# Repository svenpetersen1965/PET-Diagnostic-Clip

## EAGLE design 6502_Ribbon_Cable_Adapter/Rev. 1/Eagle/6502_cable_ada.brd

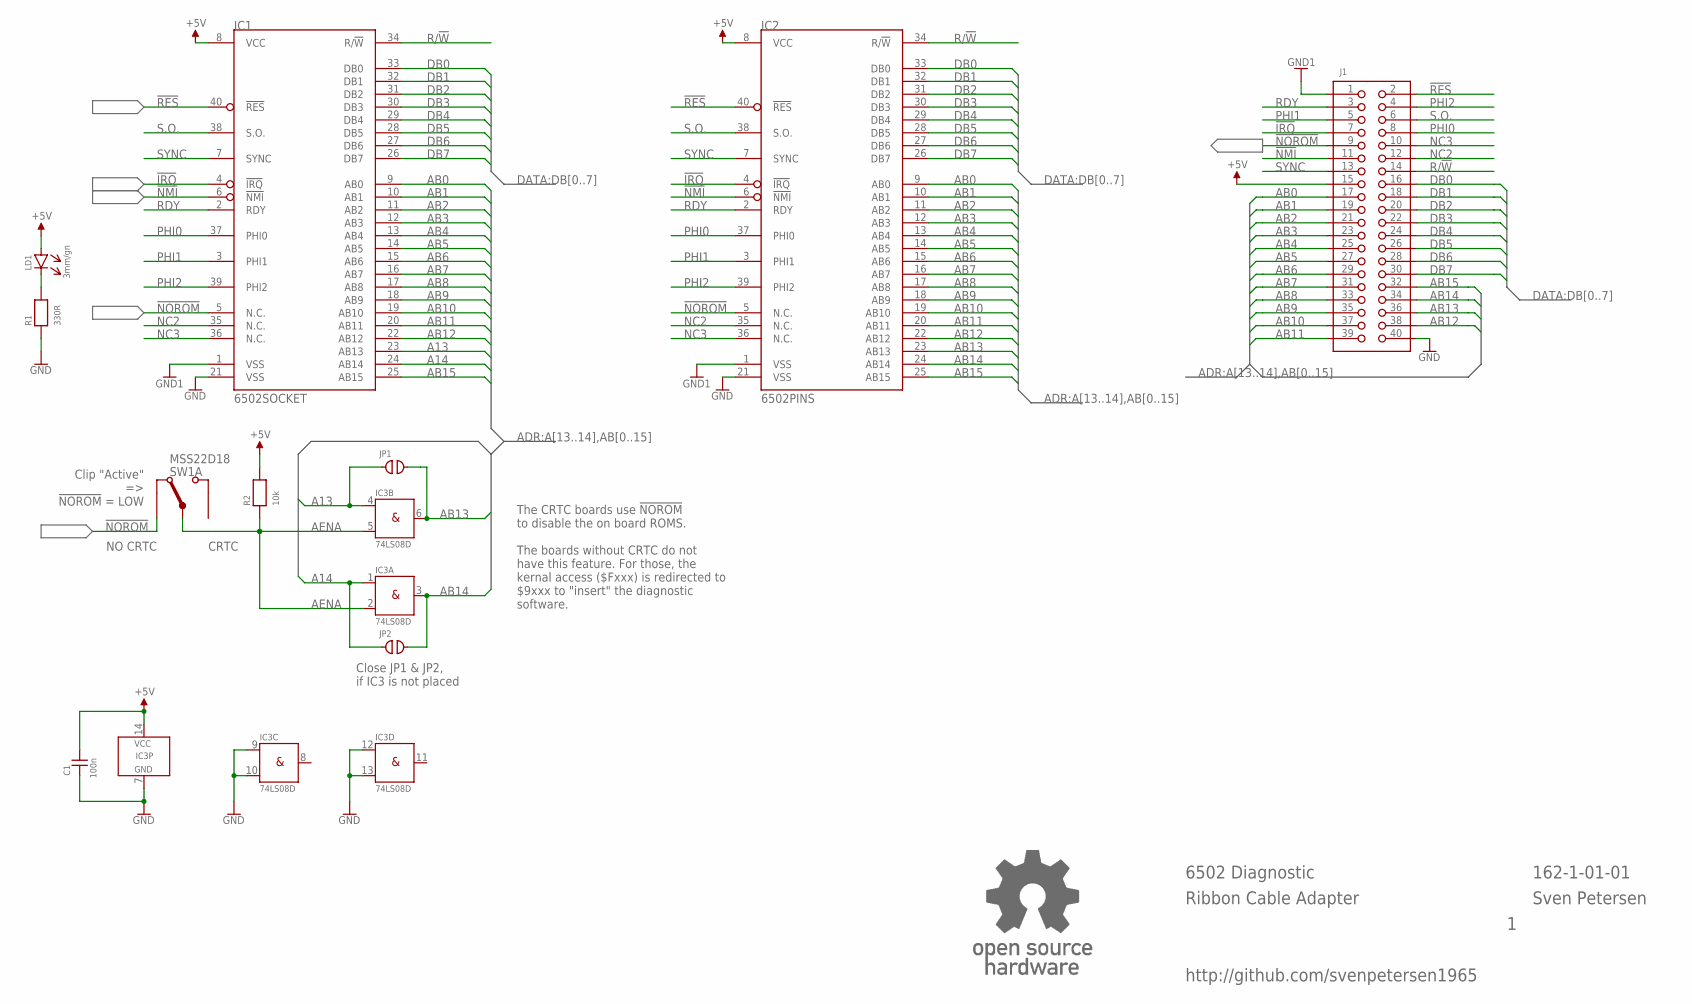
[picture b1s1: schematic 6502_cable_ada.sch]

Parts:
C1: 100n; 0805
IC1: 6502SOCKET; GS40P
IC2: 6502PINS; DIL40_PINS_SS
IC3: 74LS08D; SO-14
J1: PINHD-2X20WV; 2X20WV
JP1, JP2: OPEN; CP_OP
LD1: 3mm/gn; 3MM
R1: 330R; 0805
R2: 10k; 0805
SW1: MSS22D18; DPDT_9MM
U$11: OPEN_SOURCE_HW; OPENHW

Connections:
!IRQ: IC1.4 (!IRQ), IC2.4 (!IRQ), J1.7
!NMI: IC1.6 (!NMI), IC2.6 (!NMI), J1.11
!NOROM: IC1.5 (N.C.), IC2.5 (N.C.), J1.9, SW1.3 (DWN)
!RES: IC1.40 (!RES), IC2.40 (!RES), J1.2
+5V: C1.2, IC1.8 (VCC), IC2.8 (VCC), IC3.14 (VCC), J1.15, LD1.A, R2.2
A13: IC1.23 (AB13), IC3.4 (I0), JP1.1
A14: IC1.24 (AB14), IC3.1 (I0), JP2.1
AB0: IC1.9 (AB0), IC2.9 (AB0), J1.17
AB1: IC1.10 (AB1), IC2.10 (AB1), J1.19
AB2: IC1.11 (AB2), IC2.11 (AB2), J1.21
AB3: IC1.12 (AB3), IC2.12 (AB3), J1.23
AB4: IC1.13 (AB4), IC2.13 (AB4), J1.25
AB5: IC1.14 (AB5), IC2.14 (AB5), J1.27
AB6: IC1.15 (AB6), IC2.15 (AB6), J1.29
AB7: IC1.16 (AB7), IC2.16 (AB7), J1.31
AB8: IC1.17 (AB8), IC2.17 (AB8), J1.33
AB9: IC1.18 (AB9), IC2.18 (AB9), J1.35
AB10: IC1.19 (AB10), IC2.19 (AB10), J1.37
AB11: IC1.20 (AB11), IC2.20 (AB11), J1.39
AB12: IC1.22 (AB12), IC2.22 (AB12), J1.38
AB13: IC2.23 (AB13), IC3.6 (O), J1.36, JP1.2
AB14: IC2.24 (AB14), IC3.3 (O), J1.34, JP2.2
AB15: IC1.25 (AB15), IC2.25 (AB15), J1.32
AENA: IC3.2 (I1), IC3.5 (I1), R2.1, SW1.2 (COM)
DB0: IC1.33 (DB0), IC2.33 (DB0), J1.16
DB1: IC1.32 (DB1), IC2.32 (DB1), J1.18
DB2: IC1.31 (DB2), IC2.31 (DB2), J1.20
DB3: IC1.30 (DB3), IC2.30 (DB3), J1.22
DB4: IC1.29 (DB4), IC2.29 (DB4), J1.24
DB5: IC1.28 (DB5), IC2.28 (DB5), J1.26
DB6: IC1.27 (DB6), IC2.27 (DB6), J1.28
DB7: IC1.26 (DB7), IC2.26 (DB7), J1.30
GND: C1.1, IC1.21 (VSS), IC2.21 (VSS), IC3.7 (GND), IC3.9 (I0), IC3.10 (I1), IC3.12 (I0), IC3.13 (I1), J1.40, R1.1
GND1: IC1.1 (VSS), IC2.1 (VSS), J1.1
unnamed: LD1.C (K), R1.2
NC2: IC1.35 (N.C.), IC2.35 (N.C.), J1.12
NC3: IC1.36 (N.C.), IC2.36 (N.C.), J1.10
PHI0: IC1.37 (PHI0), IC2.37 (PHI0), J1.8
PHI1: IC1.3 (PHI1), IC2.3 (PHI1), J1.5
PHI2: IC1.39 (PHI2), IC2.39 (PHI2), J1.4
R/!W: IC1.34 (R/!W), IC2.34 (R/!W), J1.14
RDY: IC1.2 (RDY), IC2.2 (RDY), J1.3
S.O.: IC1.38 (S.O.), IC2.38 (S.O.), J1.6
SYNC: IC1.7 (SYNC), IC2.7 (SYNC), J1.13

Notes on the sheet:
6502 Diagnostic
Ribbon Cable Adapter
Sven Petersen
162-1-01-01
http://github.com/svenpetersen1965
Close JP1 & JP2, if IC3 is not placed
Clip "Active" => !NOROM! = LOW
CRTC
NO CRTC
The CRTC boards use !NOROM! to disable the on board ROMS. The boards without CRTC do not have this feature. For those, the kernal access ($Fxxx) is redirected to $9xxx to "insert" the diagnostic software.

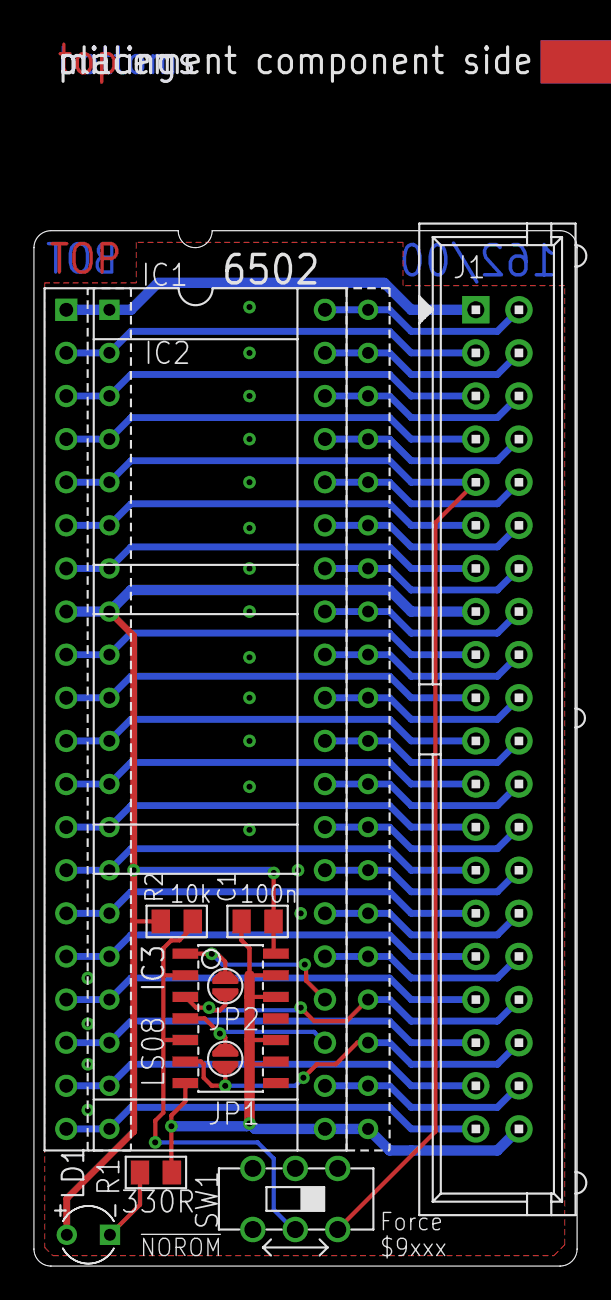
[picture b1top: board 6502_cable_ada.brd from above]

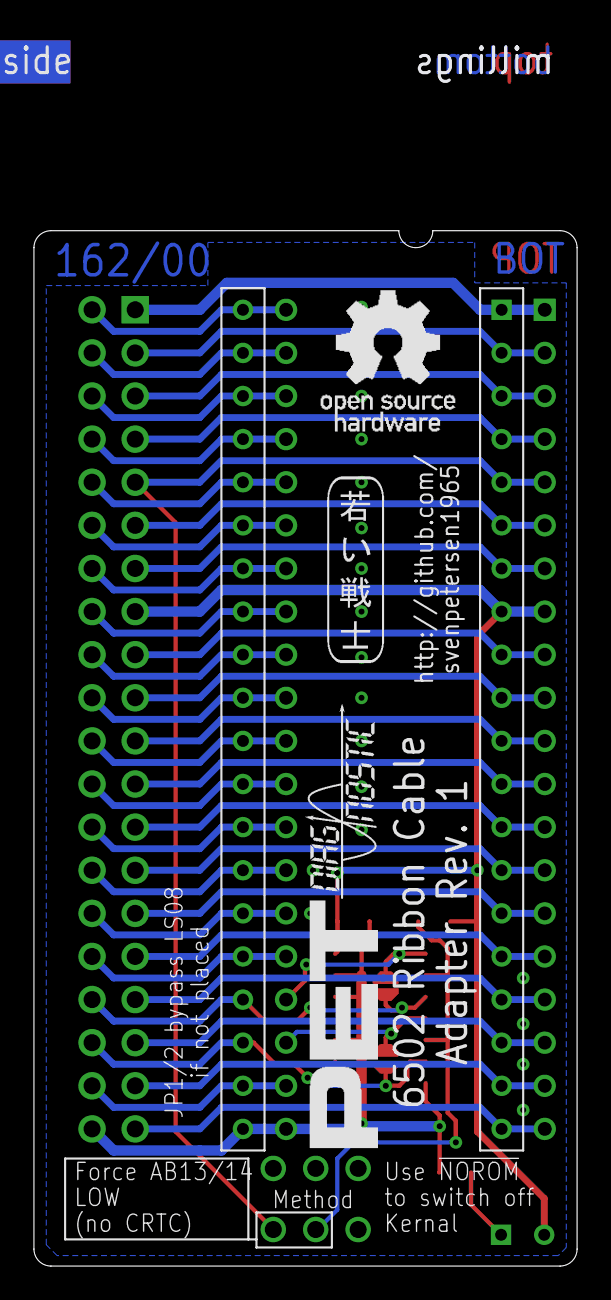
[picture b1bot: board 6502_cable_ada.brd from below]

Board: 2 copper layers, 32.0 x 61.0 mm, 17 parts (4 on the bottom side), 44 nets.

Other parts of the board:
U$12: PCB-TITLE/
U$13: 2LAYER
U$14: SVEN_TAG
U$17: DIAG_SMALL
U$29: PET

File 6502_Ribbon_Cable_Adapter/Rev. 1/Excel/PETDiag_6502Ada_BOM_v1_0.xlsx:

Commodore PET Diagnostic Clip: 6502 Ribbon Cable Adapter Rev. 1
Bill of Material Rev. 1.0
Pos. | Qty | Value | Footprint | Ref.-No. | Comment
1 | 1 | 162-2-01-01 | 2 Layer | PCB Rev. 1 | 2 layer, Cu 35µ, HASL, 61.0mm x 32.0mm, 1.6mm FR4
2 | 1 | 2x20 box header, 2.54mm pitch | 2X20WV | J1 | 2x20, box pin header or standard pin header, e.g. reichelt.de WSL 40G
3 | 1 | 330R | 0805 | R1 | SMD, 1/8W, 5%
4 | 1 | 3mm/gn | 3MM | LD1 | standard LED 3mm/green
5 | 1 | 6502PINS | DIL40_PINS_SS | IC2 | Precision round pin header, e.G. bkl-electronic.de Art.-Nr. 10120540, Reichelt 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
6 | 1 | DIP40 socket | GS40P | IC1 | Socket for 6502
7 | 1 | 10k | 0805 | R2 | SMD, 1/8W, 5%
8 | 1 | 100n | 0805 | C1 | SMD
9 | 1 | 74LS08D | SO-14 | IC3 | SMD IC, e.g. TI
10 | 1 | mini slide switch, 2.54mm, DPDT, through hole |  | SW1 | Ali Express, ebay, Amazon, search term "MSS22D18", see module description
 |  | Rev. History
 |  | Rev. 1
Pos | 3 | now 0805
Pos | 7 | new
Pos | 8 | new
Pos | 9 | new
Pos | 10 | new
